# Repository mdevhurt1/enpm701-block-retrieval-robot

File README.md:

# ENPM 701 Grand Challenge -- Final Project

## Overview

Autonomous Raspberry Pi 4B robot that locates colored blocks (red, green, blue) in a 7x7 ft arena,
picks them up, and delivers them to the NW collection zone. Starts from the SW launch
zone. Uses pigpio for hardware-timed encoder counting and wall-proximity localization.

## Results

Recorded paths from two full runs (launch zone bottom left, collection zone top left):

| Run 1 | Run 2 |
|---|---|
|  |  |

Timelapses with detection overlay: [run 1](timelapse1.mp4), [run 2](timelapse2.mp4).

## Hardware

- `CAD/`: FreeCAD model and printable STL mounts (Pi, camera, gripper, H-bridge, ultrasonic, battery cage)
- `Electrical/`: KiCad schematic and board layout
- `arduino/imu_serial/`: Arduino sketch that streams IMU heading over serial

## Requirements

- Raspberry Pi with pigpiod running (`sudo pigpiod`)
- Dev and test packages: `pip install -r requirements-dev.txt`
- On the Pi, also: `pigpio`, `picamera2` (with libcamera), and `pyserial`

## Running the mission

```bash
sudo pigpiod          # start pigpio daemon if not running
python main.py        # autonomous run
python -m fp          # equivalent
```

## Package layout

```
.
|-- main.py
|-- fp/
|   |-- arena.py        # arena geometry, zone bounds, coordinate math
|   |-- cli.py          # startup, hardware init, run loop
|   |-- fsm.py          # mission state machine
|   |-- hal.py          # pigpio GPIO, motors, encoders, ultrasonic, IMU, servo
|   |-- localization.py # pose tracking, wall-clearance checks
|   |-- mapping.py      # path recording and PNG visualization
|   |-- motion.py       # drive, pivot, localize, approach, grab, release
|   |-- search.py       # grid-based search planner, 360-degree scan
|   \-- vision.py       # camera capture, HSV blob detection
\-- calibration/
    |-- calibrate_camera.py     # compute and save camera intrinsics (checkerboard)
    |-- blob_size.py            # display blob area and centroid readings live
    |-- capture_full_res.py     # capture full-res frames under every AWB mode
    |-- encoder_test.py         # verify encoder counts per revolution
    |-- extract_hsv.py          # polygon-masked HSV range extraction
    |-- hsv_tuner.py            # live trackbar HSV tuner (requires Pi camera)
    |-- hsv_tuner_static.py     # trackbar HSV tuner on a saved JPEG
    |-- make_timelapse.py       # stitch timelapse frames with detection overlay
    |-- ultrasonic_test.py      # print live ultrasonic readings
    \-- vision_sample.py        # capture frame, detect blocks, save masks
```

`tests/` holds the pytest suite; `scripts/verify.sh` runs the checks.

## Running tests

```bash
python -m pytest tests/ -v
```

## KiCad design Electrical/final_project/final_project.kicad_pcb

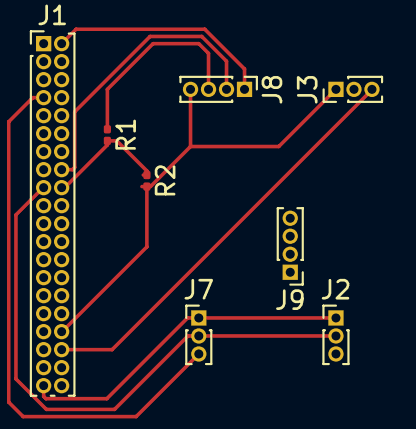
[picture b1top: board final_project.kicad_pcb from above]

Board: 2 copper layers, 8 parts (0 on the bottom side), 13 nets.

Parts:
J1: Raspberry_Pi_4b; PinHeader_2x20_P1.00mm_Vertical
J2: Back_Right_Encoder; PinHeader_1x03_P1.00mm_Vertical
J3: Servo; PinHeader_1x03_P1.00mm_Vertical
J7: Front_Left_Encoder; PinHeader_1x03_P1.00mm_Vertical
J8: Ultrasonic; PinHeader_1x04_P1.00mm_Vertical
J9: H-Bridge; PinHeader_1x04_P1.00mm_Vertical
R1: 1k; R_0201_0603Metric
R2: 2k; R_0201_0603Metric

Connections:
/3.3V: J1.1, J1.17, J2.2, J7.2
/5v: J1.2, J8.1
/BRENC: J1.12, J2.3
/ECHO: J1.18, R1.2, R2.1
/FLENC: J1.7, J7.3
/GND: J1.6, J1.9, J1.14, J1.34, J1.39, J2.1, J3.1, J7.1, J8.4, R2.2
/IN1: J1.31, J9.4
/IN2: J1.33, J9.3
/IN3: J1.35, J9.2
/IN4: J1.37, J9.1
/Servo: J1.36, J3.3
/TRIG: J1.16, J8.2
unnamed: J8.3, R1.1

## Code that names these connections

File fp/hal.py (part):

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_ENCODER_GLITCH_US      = 300

# Ultrasonic sensor
_TRIG               = 23  # Board 16
_ECHO               = 24  # Board 18
_ULTRASONIC_TIMEOUT = 0.02

# Gripper servo (BCM)
_SERVO_PIN         = 16    # Board 36
_GRIPPER_OPEN_US   = 1500  # 7.5% duty at 50 Hz
_GRIPPER_CLOSED_US = 700   # 3.5% duty at 50 Hz

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        br_cb = self._pi.callback(_BACK_RIGHT_ENCODER_PIN, pigpio.RISING_EDGE, self._on_encoder)
        self._encoder_callbacks = [fl_cb, br_cb]

        self._pi.set_mode(_TRIG, pigpio.OUTPUT)
        self._pi.set_mode(_ECHO, pigpio.INPUT)
        self._pi.write(_TRIG, 0)

        self._pi.set_mode(_SERVO_PIN, pigpio.OUTPUT)
        self._pi.set_servo_pulsewidth(_SERVO_PIN, _GRIPPER_OPEN_US)

    def cleanup(self) -> None:
        self.stop_motors()
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            cb.cancel()
        self._encoder_callbacks.clear()

        self._pi.set_servo_pulsewidth(_SERVO_PIN, 0)
        self._pi.stop()

    def stop_motors(self) -> None:
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
    def gripper_open(self) -> None:
        if self._pi:
            self._pi.set_servo_pulsewidth(_SERVO_PIN, _GRIPPER_OPEN_US)

    def gripper_close(self) -> None:
        if self._pi:
            self._pi.set_servo_pulsewidth(_SERVO_PIN, _GRIPPER_CLOSED_US)

    def gripper_set(self, duty: float) -> None:
        if self._pi:
            pulsewidth_us = int(duty / 100.0 * 20000)
            self._pi.set_servo_pulsewidth(_SERVO_PIN, pulsewidth_us)

    def start_ultrasonic(self, timeout_s: int = 10) -> bool:
        self._ultrasonic_thread = threading.Thread(
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
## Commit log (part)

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2026-04-25 Add final project
2026-05-05 Migrate HAL to pigpio, refactor subsystems, and initial tuning
2026-05-05 Final hardware tuning, localization improvements, and test suite
2026-05-06 Reorganize repo, add READMEs, and clean up code
2026-05-06 Added grand challenge report
